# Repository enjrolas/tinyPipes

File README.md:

## TinyPipes git repo
===

Welcome to the tinyPipes git repo!  This is the home of all the hardware and firmware for tinyPipes electronics.  This should give you a basic idea of where everything lives, and how to use the repo.  Ready?  Onwards!

The repo has a pretty simple structure:

	/
	|
	+Firmware/
	|	|
	|	+bootloader/
	|	|
	|	+libraries/
	|	|
	|	+utilities/
	|	|
	|	+wetware/
	|	|
	|	+Shipped Firmware/
	|
	+Hardware/
		|
		+gerbers/
		|
		+demo/
		|
		+proto/

Firmware/

This is where all firmware lives.  The tinyPipes firmware is called wetware.  It's all based around Arduino C and compilable in arduino 1.0 and later.  

Install everything in libraries/ into the libraries folder in your Arduino sketch folder.

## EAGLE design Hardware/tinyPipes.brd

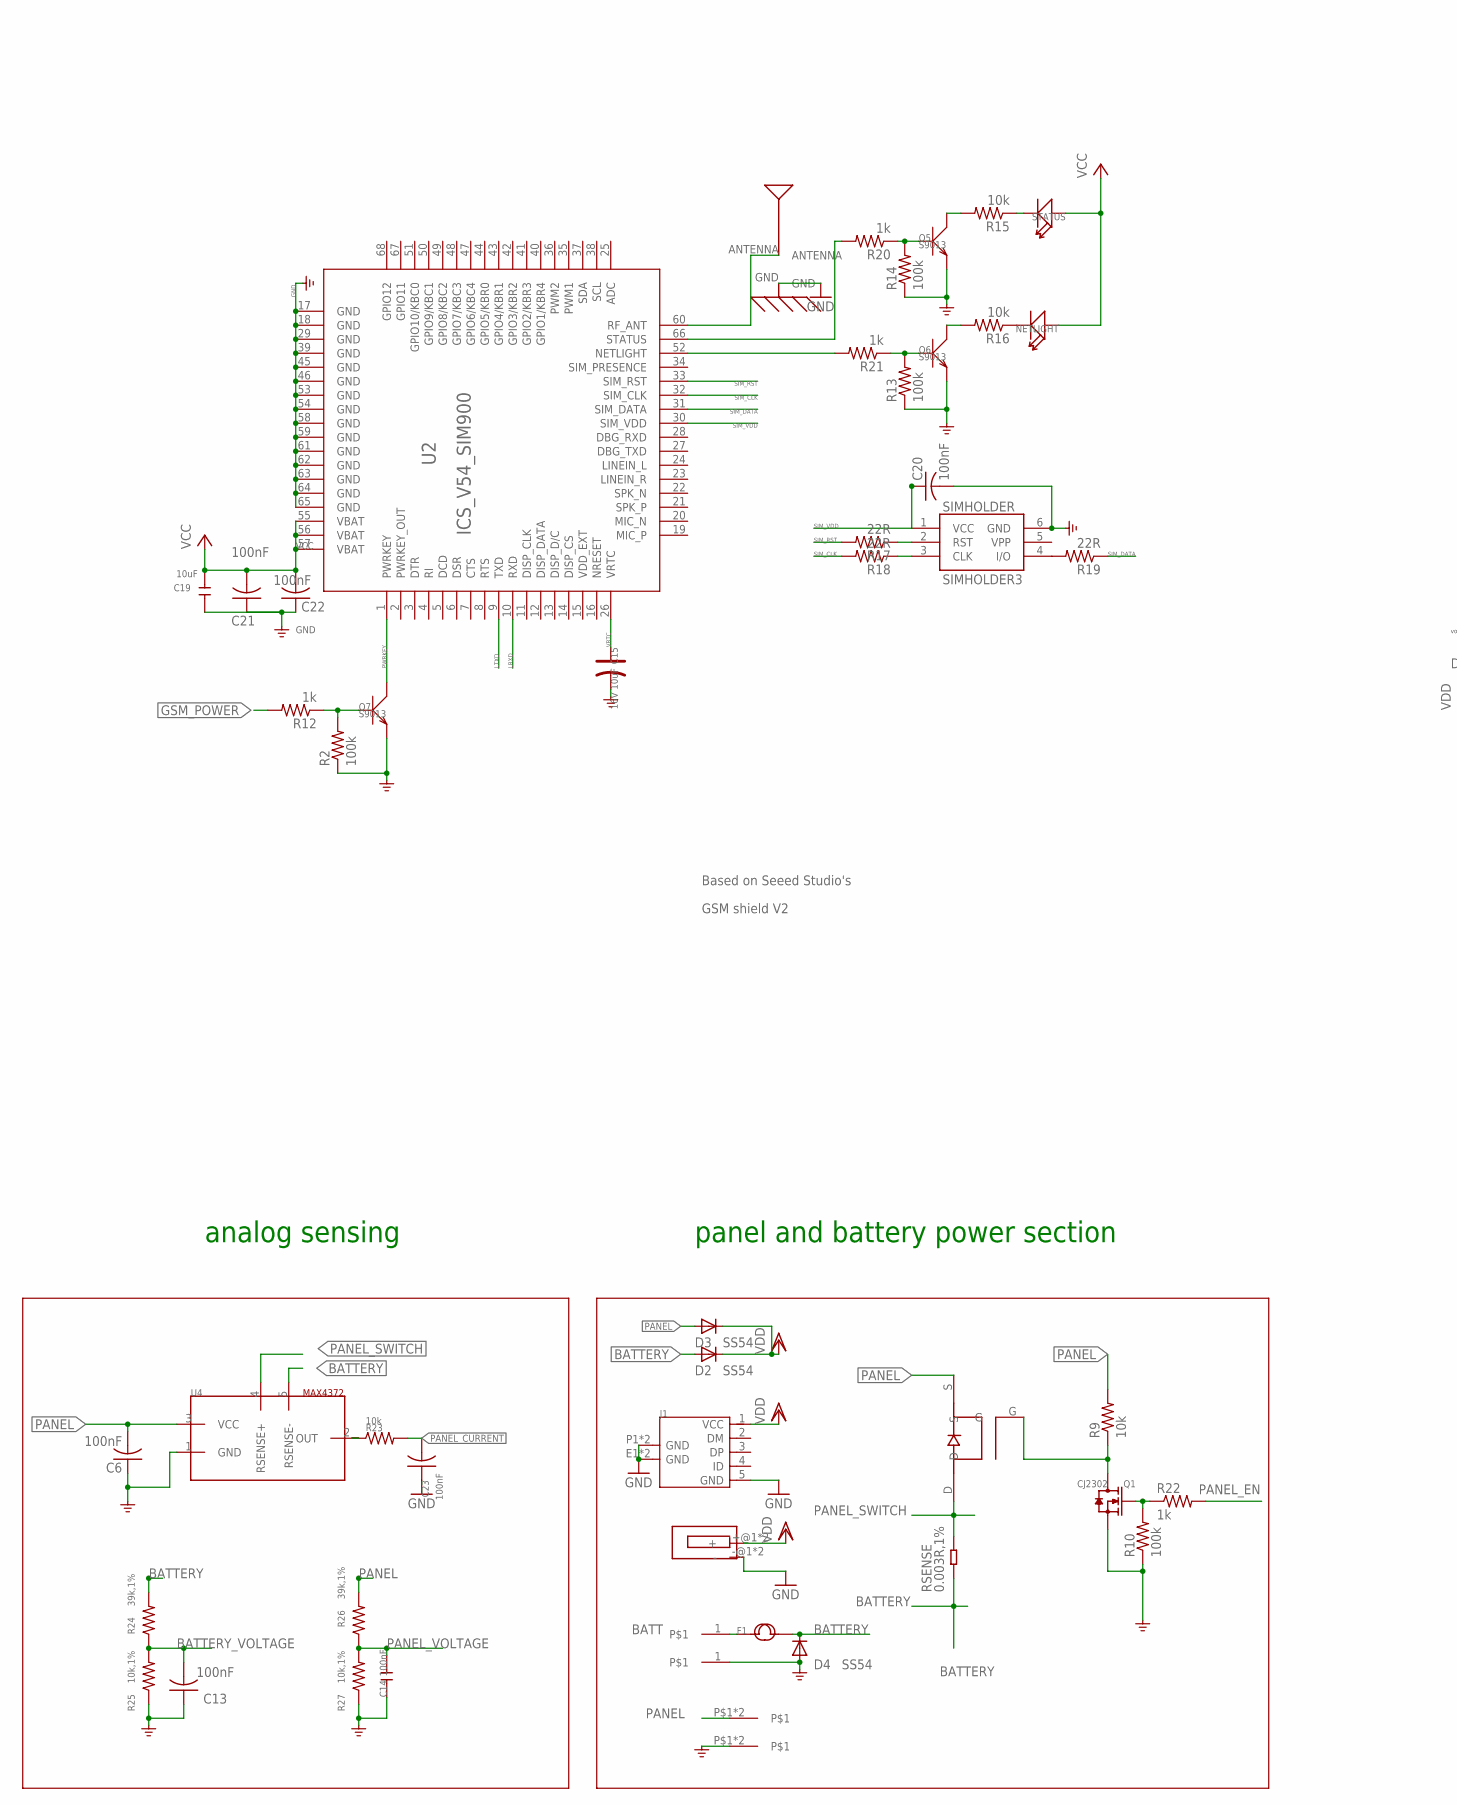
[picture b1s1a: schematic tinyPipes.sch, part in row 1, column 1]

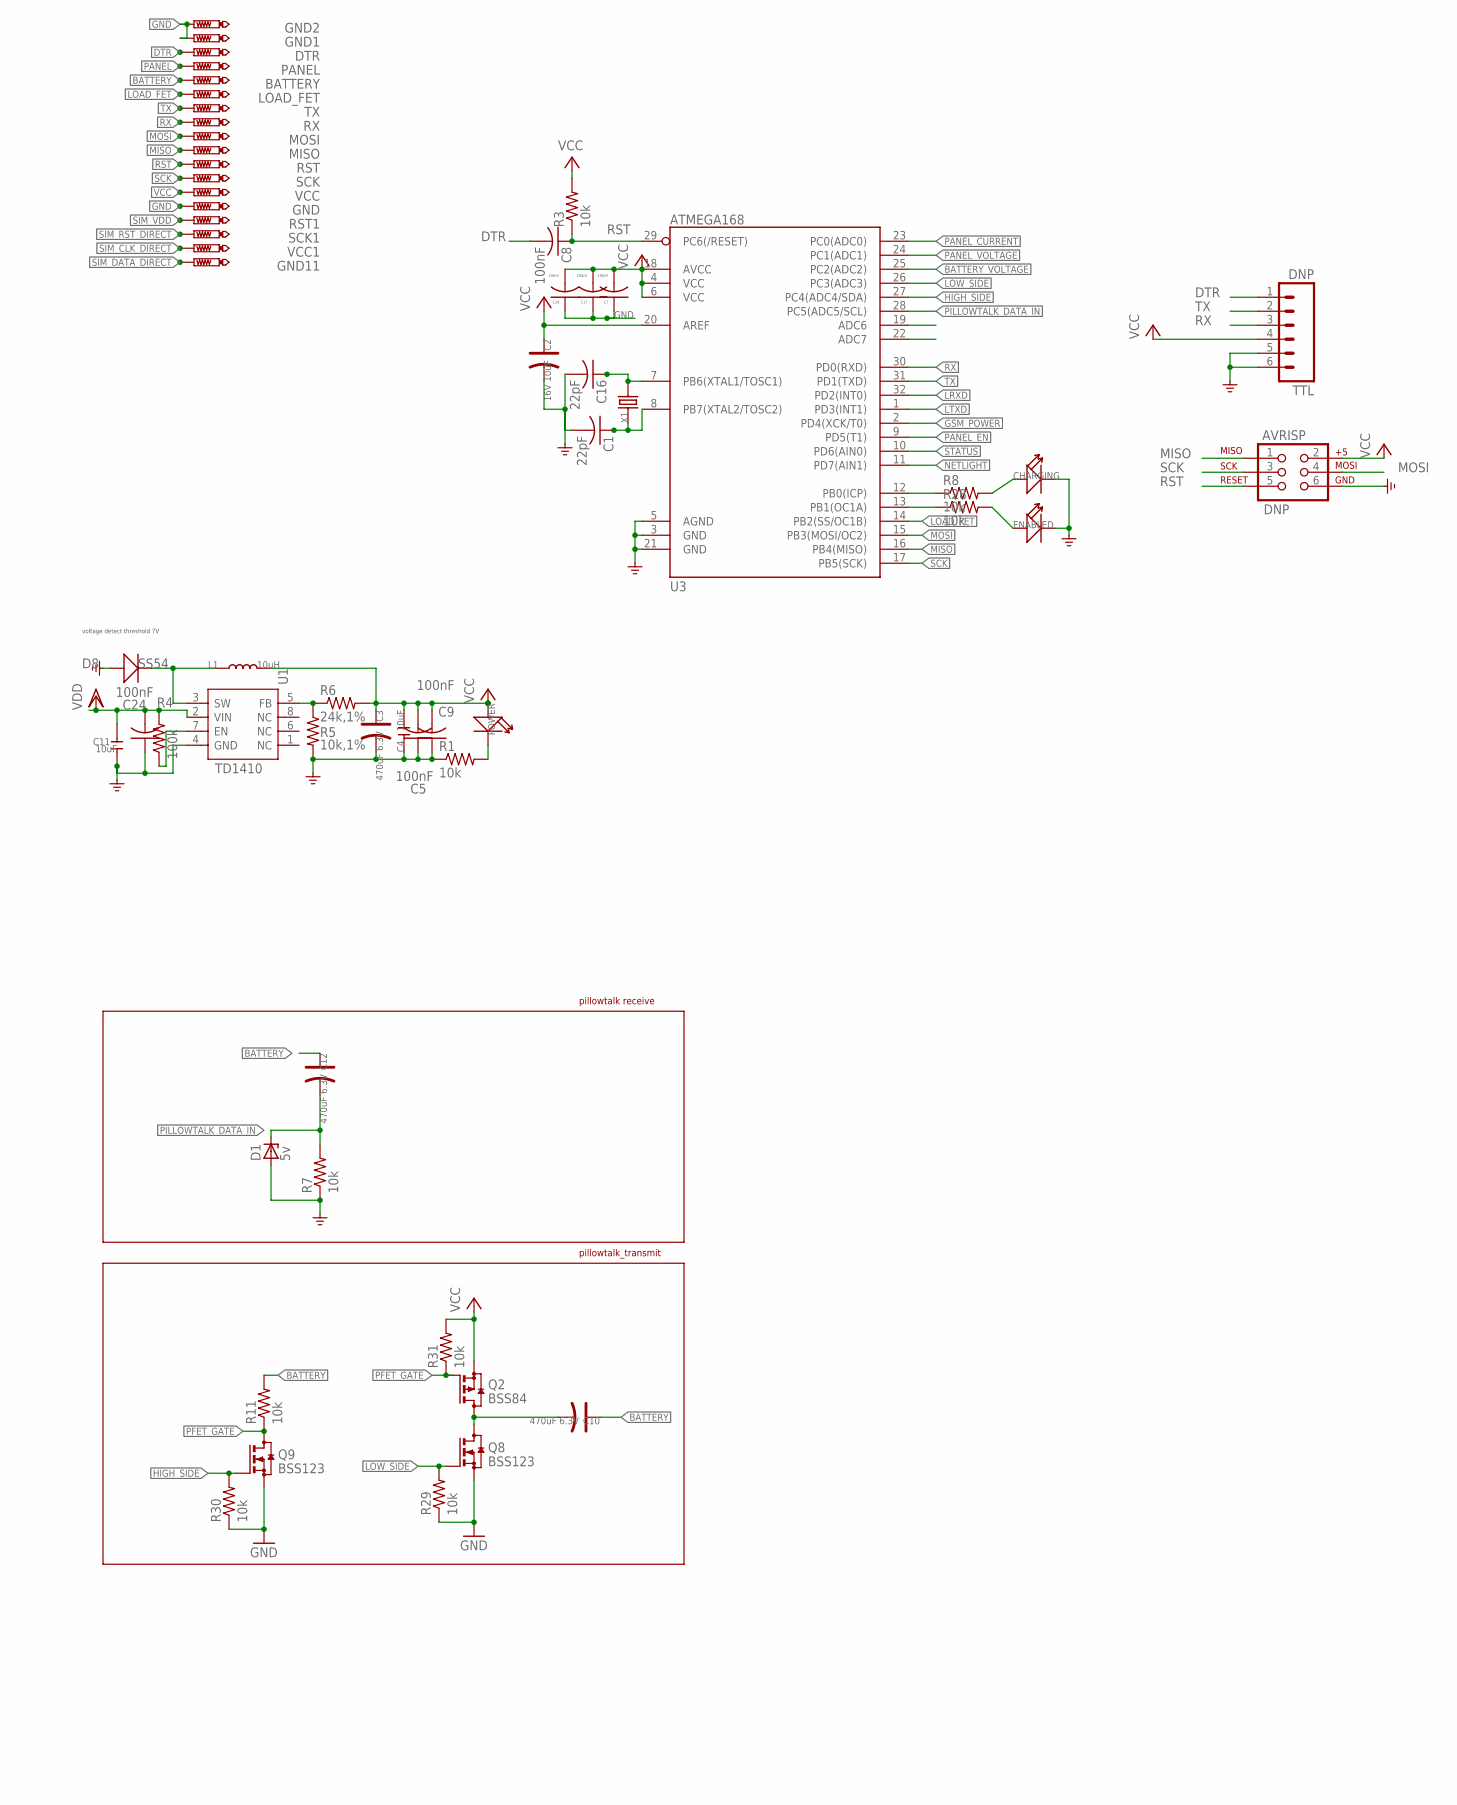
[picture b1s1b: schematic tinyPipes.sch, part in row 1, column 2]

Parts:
AVRISP: DNP; 2X3_LOCK
BATTERY: HEARTPAD; HEART
BATTERY+: TINYPIPES_BATTBATT; TINYPIPES_BATT
BATTERY-: TINYPIPES_BATTBATT; TINYPIPES_BATT
C1, C16: 22pF; C0402
C2, C15: 16V 10uF; AVX-A
C3, C10, C12: 470uF 6.3V; AVX-D
C4, C11, C19: 10uF; C0805
C5, C6, C7, C8, C9, C13, C17, C18, C20, C21, C22, C23, C24: 100nF; C0402
C14: 100nF; C0603
CHARGING: LED'0603'; LED-0603
D1: 5v; SOT23
D2, D3, D4, D8: SS54; SMB
DTR: HEARTPAD; HEART
ENABLED: LED'0603'; LED-0603
F1: FUSE'16R700'; 0210
GND, GND1, GND2, GND11: HEARTPAD; HEART
J1: Micro-USB connector; B-SMD-5P
L1: 10uH; L0630
LOAD_FET: HEARTPAD; HEART
MISO: HEARTPAD; HEART
MOSI: HEARTPAD; HEART
NETLIGHT: LED'0603'; LED-0603
PANEL: HEARTPAD; HEART
PANEL+: TINYPIPES_BATTPANEL; TINYPIPES_PANEL
PANEL-: TINYPIPES_BATTPANEL; TINYPIPES_PANEL
POWER: LED'0603'; LED-0603
Q1: CJ2302; SOT23
Q2: BSS84; SOT23
Q5, Q6, Q7: S9013; SOT23
Q8, Q9: BSS123; SOT23
R1, R3, R7, R8, R9, R11, R15, R16, R23, R28, R29, R30, R31: 10k; R0402
R2, R4, R10, R13, R14: 100k; R0402
R5, R25, R27: 10k,1%; R0402
R6: 24k,1%; R0402
R12, R20, R21, R22: 1k; R0402
R17, R18, R19: 22R; R0402
R24, R26: 39k,1%; R0402
RSENSE: 0.003R,1%; R2512
RST, RST1: HEARTPAD; HEART
RX: HEARTPAD; HEART
SCK, SCK1: HEARTPAD; HEART
SIMHOLDER: SIMHOLDER3
STATUS: LED'0603'; LED-0603
TTL: DNP; 1X06_LOCK
TX: HEARTPAD; HEART
U1: TD1410; SOP8
U2: ICS_V54_SIM900
U3: ATMEGA168; TQFP32-08
U4: MAX4372; SOT23-5
U5: SI4435POWER; SO8_FET
U$1: PCB_ANTENNA; GSM_PCB_ANTENNA
U$4: BARREL_JACK; BARREL_PLUG
VCC, VCC1: HEARTPAD; HEART
X1: CRYSTAL'5032'; 2P-SMD-5X3.2

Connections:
ALT5: U3.22 (ADC7)
BATT: BATTERY+.1, F1.1
BATTERY: BATTERY.P$1, C10.+, C12.+, D2.A, D4.C, F1.2, R11.2, R24.2, RSENSE.1, U4.5 (RSENSE-)
BATTERY_VOLTAGE: C13.2, R24.1, R25.2, U3.25 (PC2(ADC2))
DTR: C8.2, DTR.P$1, TTL.1
GND: AVRISP.6, BATTERY-.1, C1.2, C2.-, C3.-, C4.1, C5.1, C6.1, C7.1, C9.1, C11.1, C13.1, C14.1, C15.-, C16.2, C17.1, C18.1, C19.1, C20.2, C21.1, C22.1, C23.1, C24.1, CHARGING.-, D1.1 (A), D4.A, D8.+, ENABLED.-, GND.P$1, GND1.P$1, GND2.P$1, J1.5 (GND), J1.E1 (GND), J1.E2 (GND), J1.P1 (GND), J1.P2 (GND), PANEL-.P$1, PANEL-.P$2, Q1.2 (S), Q5.2 (E), Q6.2 (E), Q7.2 (E), Q8.2 (S), Q9.2 (S), R1.1, R2.1, R5.2, R7.1, R10.1, R13.1, R14.1, R25.1, R27.1, R29.1, R30.1, SIMHOLDER.6 (GND), TTL.5, TTL.6, U1.4 (GND), U2.17 (GND), U2.18 (GND), U2.29 (GND), U2.39 (GND), U2.45 (GND), U2.46 (GND), U2.53 (GND), U2.54 (GND), U2.58 (GND), U2.59 (GND), U2.61 (GND), U2.62 (GND), U2.63 (GND), U2.64 (GND), U2.65 (GND), U3.3 (GND), U3.5 (AGND), U3.21 (GND), U4.1 (GND), U$1.GND, U$4.-@1 (-), U$4.-@2 (-)
GSM_POWER: R12.2, U3.2 (PD4(XCK/T0))
HIGH_SIDE: Q9.1 (G), R30.2, U3.27 (PC4(ADC4/SDA))
LOAD_FET: LOAD_FET.P$1, U3.14 (PB2(SS/OC1B))
LOW_SIDE: Q8.1 (G), R29.2, U3.26 (PC3(ADC3))
LRXD: U2.10 (RXD), U3.32 (PD2(INT0))
LTXD: U2.9 (TXD), U3.1 (PD3(INT1))
MISO: AVRISP.1, MISO.P$1, U3.16 (PB4(MISO))
MOSI: AVRISP.4, MOSI.P$1, U3.15 (PB3(MOSI/OC2))
unnamed: U2.60 (RF_ANT), U$1.ANTENNA
unnamed: C16.1, U3.7 (PB6(XTAL1/TOSC1)), X1.2
unnamed: Q6.3 (C), R16.2
unnamed: Q7.1 (B), R2.2, R12.1
unnamed: Q5.1 (B), R14.2, R20.1
unnamed: Q6.1 (B), R13.2, R21.1
unnamed: NETLIGHT.-, R16.1
unnamed: Q5.3 (C), R15.2
unnamed: POWER.-, R1.2
unnamed: R8.1, U3.12 (PB0(ICP))
unnamed: Q1.1 (G), R10.2, R22.1
unnamed: R4.1, U1.7 (EN)
unnamed: C1.1, U3.8 (PB7(XTAL2/TOSC2)), X1.1
unnamed: R28.1, U3.13 (PB1(OC1A))
unnamed: Q1.3 (D), R9.1, U5.G
unnamed: R15.1, STATUS.-
unnamed: R23.1, U4.2 (OUT)
unnamed: CHARGING.+, R8.2
unnamed: C10.-, Q2.3 (D), Q8.3 (D)
unnamed: ENABLED.+, R28.2
unnamed: D8.-, L1.1, U1.3 (SW)
unnamed: R5.1, R6.1, U1.5 (FB)
NETLIGHT: R21.2, U2.52 (NETLIGHT), U3.11 (PD7(AIN1))
PANEL: C6.2, D3.A, PANEL.P$1, PANEL+.P$1, PANEL+.P$2, R9.2, R26.2, U4.3 (VCC), U5.S
PANEL_CURRENT: C23.2, R23.2, U3.23 (PC0(ADC0))
PANEL_EN: R22.2, U3.9 (PD5(T1))
PANEL_SWITCH: RSENSE.2, U4.4 (RSENSE+), U5.D
PANEL_VOLTAGE: C14.2, R26.1, R27.2, U3.24 (PC1(ADC1))
PFET_GATE: Q2.1 (G), Q9.3 (D), R11.1, R31.1
PILLOWTALK_DATA_IN: C12.-, D1.3 (C), R7.2, U3.28 (PC5(ADC5/SCL))
PWRKEY: Q7.3 (C), U2.1 (PWRKEY)
RST: AVRISP.5, C8.1, R3.1, RST.P$1, U3.29 (PC6(/RESET))
RX: RX.P$1, TTL.3, U3.30 (PD0(RXD))
SCK: AVRISP.3, SCK.P$1, U3.17 (PB5(SCK))
SIM_CLK: R18.2, U2.32 (SIM_CLK)
SIM_CLK_DIRECT: R18.1, SIMHOLDER.3 (CLK), VCC1.P$1
SIM_DATA: R19.1, U2.31 (SIM_DATA)
SIM_DATA_DIRECT: GND11.P$1, R19.2, SIMHOLDER.4 (I/O)
SIM_RST: R17.2, U2.33 (SIM_RST)
SIM_RST_DIRECT: R17.1, SCK1.P$1, SIMHOLDER.2 (RST)
SIM_VDD: C20.1, RST1.P$1, SIMHOLDER.1 (VCC), U2.30 (SIM_VDD)
STATUS: R20.2, U2.66 (STATUS), U3.10 (PD6(AIN0))
TX: TTL.2, TX.P$1, U3.31 (PD1(TXD))
VCC: AVRISP.2, C2.+, C3.+, C4.2, C5.2, C7.2, C9.2, C17.2, C18.2, C19.2, C21.2, C22.2, L1.2, NETLIGHT.+, POWER.+, Q2.2 (S), R3.2, R6.2, R31.2, STATUS.+, TTL.4, U2.55 (VBAT), U2.56 (VBAT), U2.57 (VBAT), U3.4 (VCC), U3.6 (VCC), U3.18 (AVCC), U3.20 (AREF), VCC.P$1
VDD: C11.2, C24.2, D2.C, D3.C, J1.1 (VCC), R4.2, U1.2 (VIN), U$4.+@1 (+), U$4.+@2 (+)
VRTC: C15.+, U2.26 (VRTC)
`: U3.19 (ADC6)

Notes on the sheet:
Based on Seeed Studio's
GSM shield V2
voltage detect threshold 7V
panel and battery power section
analog sensing
pillowtalk receive
pillowtalk_transmit

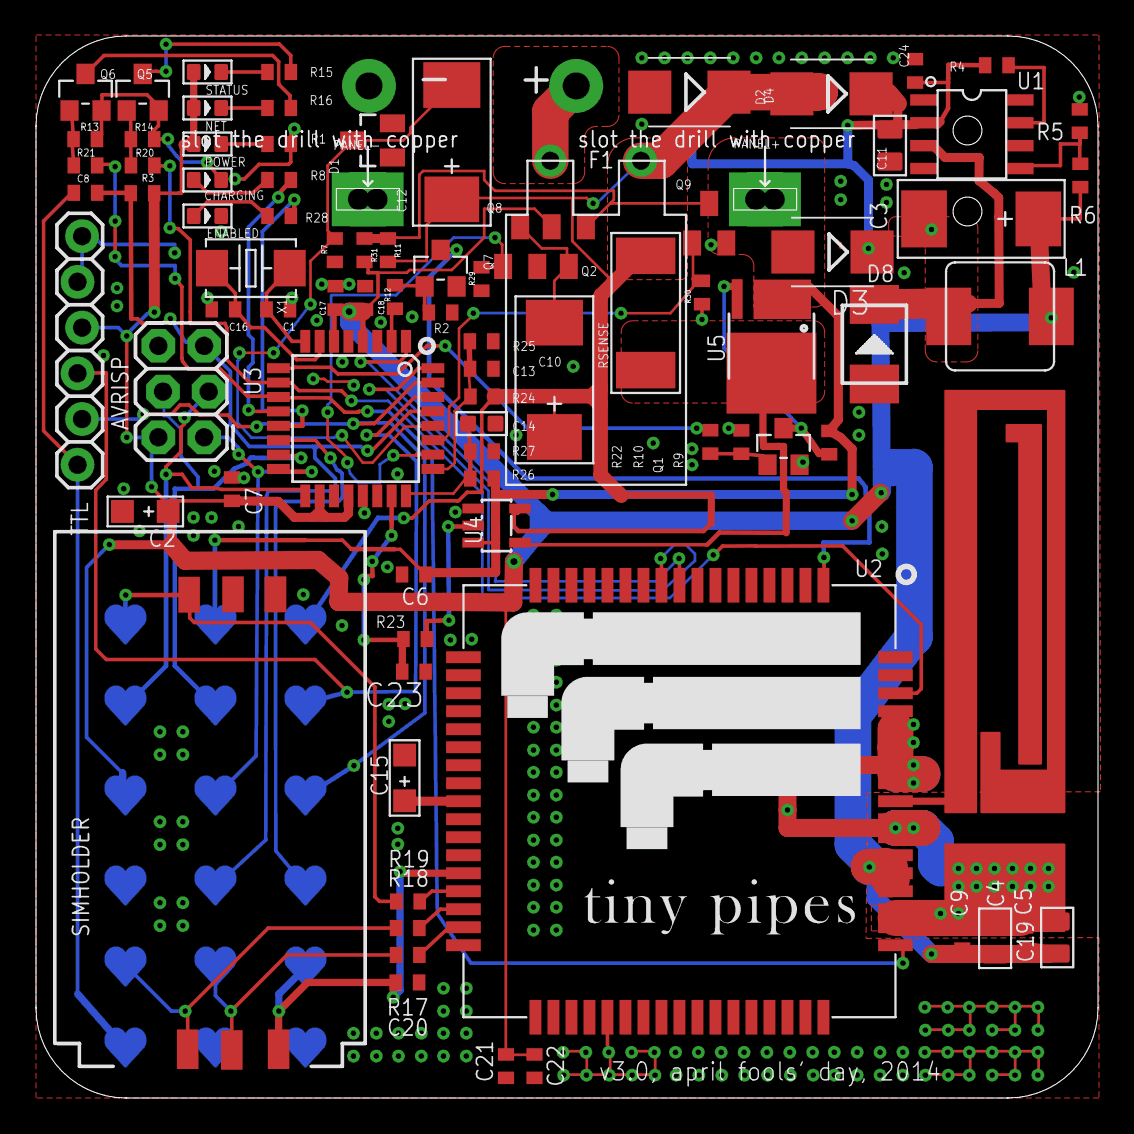
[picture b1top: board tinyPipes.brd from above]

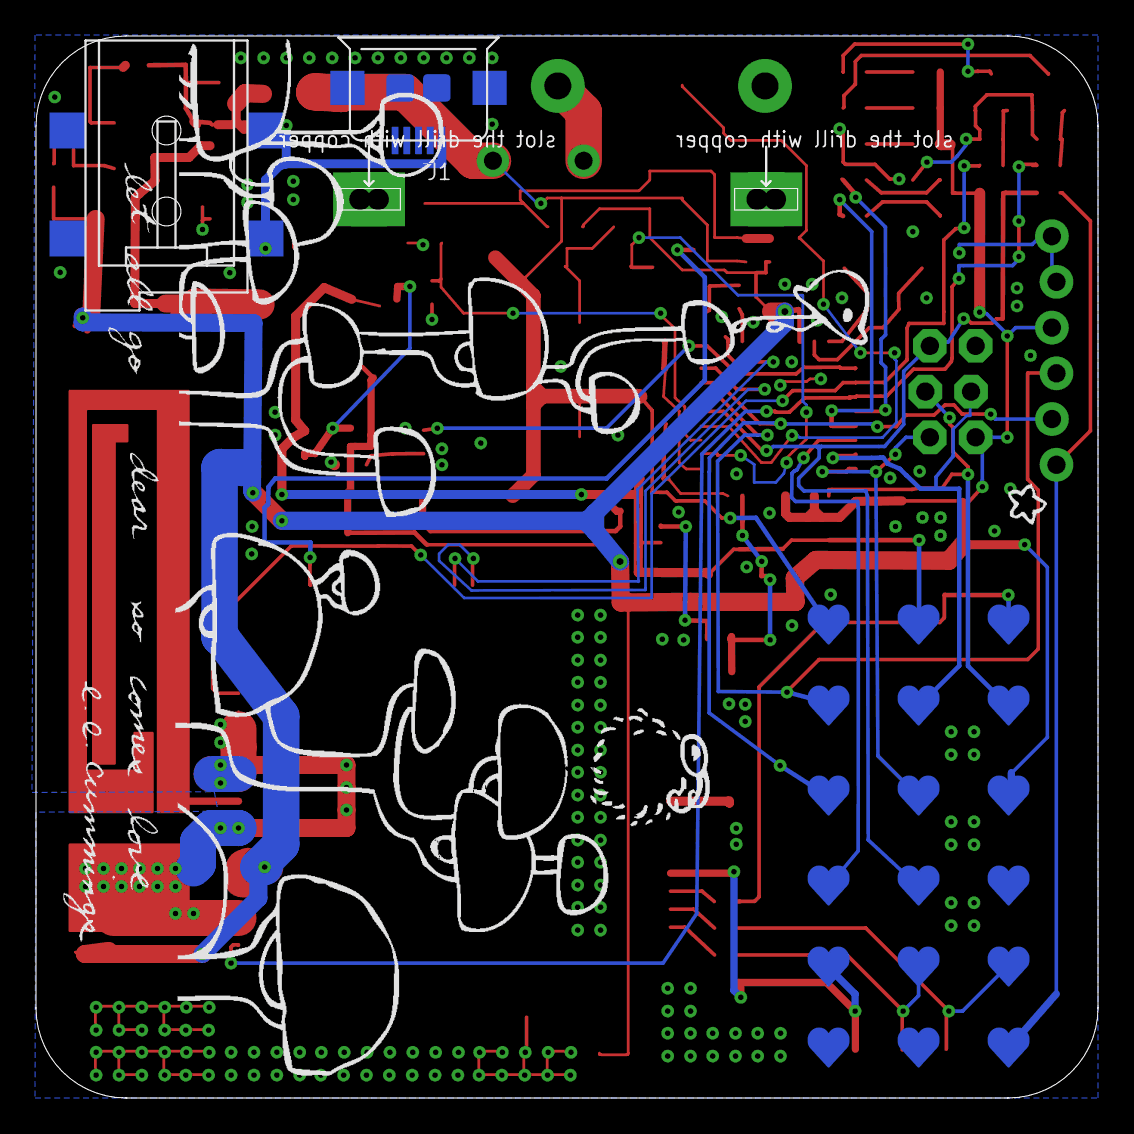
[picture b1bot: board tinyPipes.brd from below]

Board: 2 copper layers, 59.0 x 59.0 mm, 109 parts (20 on the bottom side), 59 nets.

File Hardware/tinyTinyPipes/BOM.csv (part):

Partlist

Exported from tinyPipes-tinyComponents.brd at 1/12/14 2:02 AM

EAGLE Version 6.5.0 Copyright (c) 1988-2013 CadSoft

Assembly variant: 

Part      Value               Package         Library             Position (mm)         Orientation

ANT1                          4P-U-FL         Connector           (55.29 16.74)         R0
B+        TINYPIPES_BATTBATT  TINYPIPES_BATT  tinyPipes v2.6      (30.734 56.388)       R0
B-        TINYPIPES_BATTBATT  TINYPIPES_BATT  tinyPipes v2.6      (22.225 49.53)        R0
BATTERY   PTR1B2,54           B2,54           testpad             (19 26.5)             MR0
BM        TINYPIPES_BATTSBATT TINYPIPES_SBATT tinyPipes v2.6      (24.003 42.291)       R0
BP        TINYPIPES_BATTSBATT TINYPIPES_SBATT tinyPipes v2.6      (27.972 42.489)       R0
C1        22pF                C0201           rcl                 (14.939 43.462)       R90
C2        16V 10uF            AVX-A           Discrete            (7.493 32.893)        R180
C3        470uF 6.3V          AVX-D           Discrete            (53.3895 36.953)      R180
C4        10uF                C0402           rcl                 (57.032 32.737)       R90
C5        100nF               C0402           rcl                 (55.157 32.864)       R90
C6        100nF               C0402           rcl                 (25.173 45.169)       R90
C7        100nF               C0402           rcl                 (6.866 34.346)        R0
C8        100nF               C0402           rcl                 (10.16 37.084)        R180
C9        100nF               C0402           rcl                 (53.603 32.864)       R90
C10       100nF               C0402           rcl                 (44.815 36.393)       R90
C11       10uF                C0402           rcl                 (55.513 48.5555)      R180
C12       100nF               C0402           rcl                 (36.624 36.393)       R90
C13       100nF               C0402           rcl                 (34.557 35.297)       R0
C14       100nF               C0402           rcl                 (34.577 34.145)       R0
C15       16V 10uF            AVX-A           Discrete            (25.511 18.034)       R90
C16       22pF                C0201           rcl                 (15.561 43.476)       R90
C17       100nF               C0402           rcl                 (11.637 33.45)        R270
C18       100nF               C0402           rcl                 (23.288 33.45)        R270
C19       10uF                C0805           Discrete            (53.848 11.176)       R90
C20       100nF               C0603           Discrete            (25.8275 13.1665)     R90
C21       100nF               C0402           rcl                 (57.15 11.303)        R90
C22       100nF               C0402           rcl                 (55.626 11.303)       R90
C23       100nF               C0402           rcl                 (31.204 45.291)       R270
C24       100nF               C0402           rcl                 (46.3665 48.682)      R90
C25       100nF               C0402           rcl                 (26.515 45.16)        R90
C26       0.1uF               C0402           rcl                 (27 34)               R180
D2        SS54                SMB             diode               (45.742 55.886)       R180
D4        SS54                SMB             diode               (36.3 55.88)          R180
D8        SS54                SMB             Discrete            (46.577 41.876)       R90
DTR       PTR1B2,54           B2,54           testpad             (9 3)                 MR0
F1                            0210            tinyPipes v2.6      (31.369 52.07)        R0
F2                            0210            tinyPipes v2.6      (2.731 53.213)        R90
GND       PTR1B2,54           B2,54           testpad             (9 12)                MR0
GND2      PTR1B2,54           B2,54           testpad             (14 3)                MR0
GND3      PTR1B2,54           B2,54           testpad             (19 3)                MR0
GND11     PTR1B2,54           B2,54           testpad             (9 26.5)              MR0
L1        10uH                L0630           Discrete            (53.727 42.6655)      R0
LOAD_FET  PTR1B2,54           B2,54           testpad             (19 12)               MR0
MISO      PTR1B2,54           B2,54           testpad             (14 17)               MR0
MOSI      PTR1B2,54           B2,54           testpad             (14 22)               MR0
NETLIGHT                      LED-0603        Discrete            (2.589 39.482)        R270
OUT+      TINYPIPES_BATTBATT  TINYPIPES_BATT  tinyPipes v2.6      (2.683 46.8)          R0
OUT-      TINYPIPES_BATTBATT  TINYPIPES_BATT  tinyPipes v2.6      (22.225 52.578)       R0
PANEL     PTR1B2,54           B2,54           testpad             (14 26.5)             MR0
PANEL+    TINYPIPES_BATTPANEL TINYPIPES_PANEL tinyPipes_v2.5      (40.504 49.928)       R180
PANEL-    TINYPIPES_BATTPANEL TINYPIPES_PANEL tinyPipes_v2.5      (18.438 49.928)       R180
POWER                         LED-0603        Discrete            (0.97 39.482)         R270
Q1        CJ2302              SOT23           Discrete            (41.529 36.449)       R0
Q2        IRF5305             TO263           transistor-power    (9.382 50.097)        R180
Q3        CJ2302              SOT23           Discrete            (15.216 53.978)       R0
Q5        S9013               SOT23           Discrete            (7.329 37.116)        R270
Q6        S9013               SOT23           Discrete            (2.809 33.678)        R270
Q7        S9013               SOT23           Discrete            (47.852 32.601)       R0
R1        10k                 R0201           rcl                 (1.03 37.388)         R90
R2        100k                R0201           rcl                 (48.712 30.438)       R270
R3        10k                 R0201           rcl                 (10.671 36.08)        R180
R4        100k                R0201           rcl                 (55.226 49.765)       R0
R5        10k, 1%             R0201           rcl                 (55.08 47.483)        R0
R6        24k, 1%             R0201           rcl                 (55.06 46.93)         R0
R7        10k                 R0201           rcl                 (45.913 36.738)       R270
R8        10k                 R0201           rcl                 (30.575 48.408)       R270
R9        10k                 R0201           rcl                 (43.572 36.4095)      R90
R10       100k                R0201           rcl                 (39.185 36.4415)      R270
R11       10k                 R0201           rcl                 (37.736 36.478)       R270
R12       1k                  R0201           rcl                 (46.939 30.45)        R270
R13       100k                R0201           rcl                 (0.758 33.5855)       R90
R14       100k                R0201           rcl                 (5.229 36.972)        R90
R15       10k                 R0201           rcl                 (4.208 37.418)        R270
R16       10k                 R0201           rcl                 (2.589 37.338)        R270
R17       22R                 R0201           rcl                 (24.683 8.199)        R0
R18       22R                 R0201           rcl                 (24.683 8.962)        R0
R19       22R                 R0201           rcl                 (24.669 9.618)        R180
R20       1k                  R0201           rcl                 (11.94 39.752)        R0
R21       1k                  R0201           rcl                 (11.97 38.938)        R0
R22       1k                  R0201           rcl                 (38.465 36.449)       R90
R23       10k                 R0201           rcl                 (31.249 48.388)       R270
R24       39k, 1%             R0201           rcl                 (24.757 47.556)       R90
R25       10k, 1%             R0201           rcl                 (25.5995 47.5575)     R90
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
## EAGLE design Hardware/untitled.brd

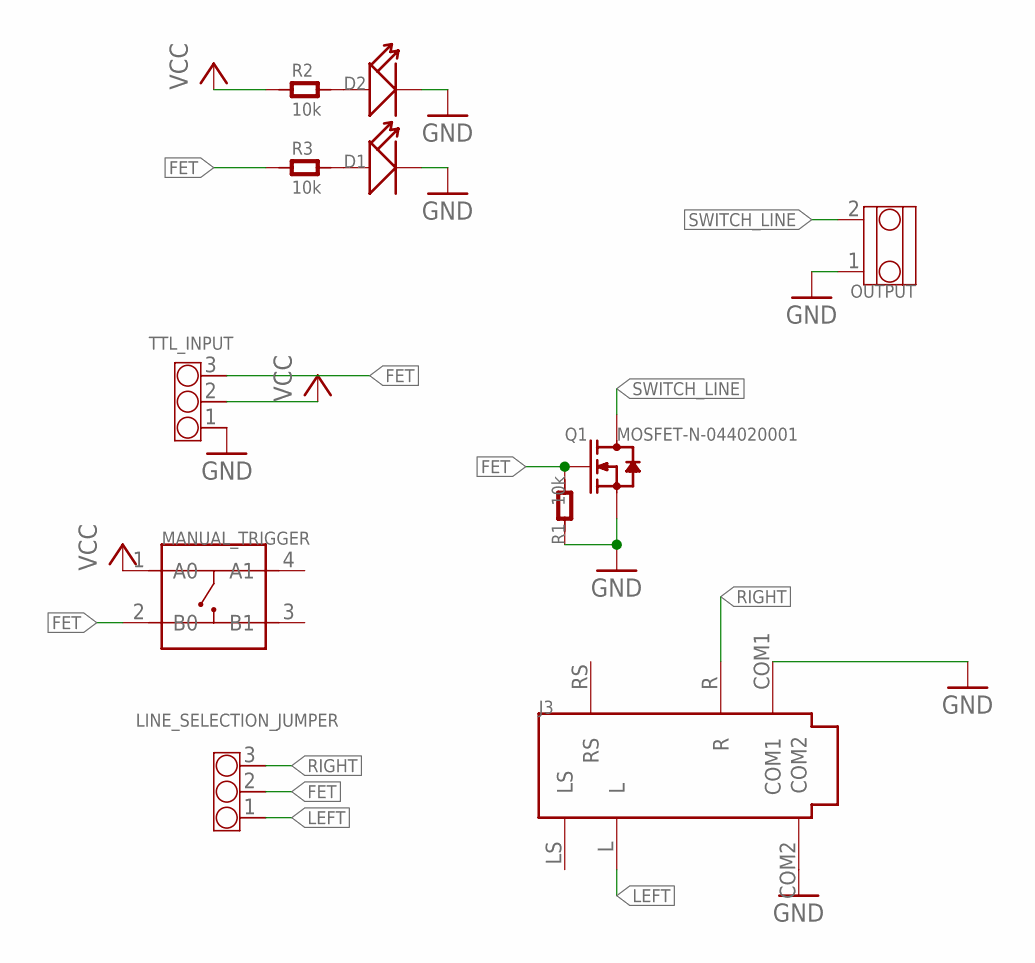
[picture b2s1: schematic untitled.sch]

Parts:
D1, D2: LED; LED0603
J3: AUDIO-CONNECTOR-6P-SMD-3440030P1; 6P-SMD-3.5
LINE_SELECTION_JUMPER: CONNECTOR-HEADER-3P-3460810P1; 1X3P-2.54-2.54-11.6-3.0-BLACK-MALE
MANUAL_TRIGGER: manual data; 4P-SMD-6.0X6.0X5.0H
OUTPUT: SCREW-TERMINAL-2P-3470070P1; 2P-3.5
Q1: MOSFET-N-044020001; SOT23
R1, R2, R3: 10k; R0603
TTL_INPUT: CONNECTOR-HEADER-3P-3460810P1; 1X3P-2.54-2.54-11.6-3.0-BLACK-MALE

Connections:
FET: LINE_SELECTION_JUMPER.2, MANUAL_TRIGGER.2 (B0), Q1.1 (G), R1.2, R3.1, TTL_INPUT.3
GND: D1.-, D2.-, J3.COM1, J3.COM2, OUTPUT.1, Q1.2 (S), R1.1, TTL_INPUT.1
LEFT: J3.L, LINE_SELECTION_JUMPER.1
unnamed: D1.+, R3.2
unnamed: D2.+, R2.2
RIGHT: J3.R, LINE_SELECTION_JUMPER.3
SWITCH_LINE: OUTPUT.2, Q1.3 (D)
VCC: MANUAL_TRIGGER.1 (A0), R2.1, TTL_INPUT.2

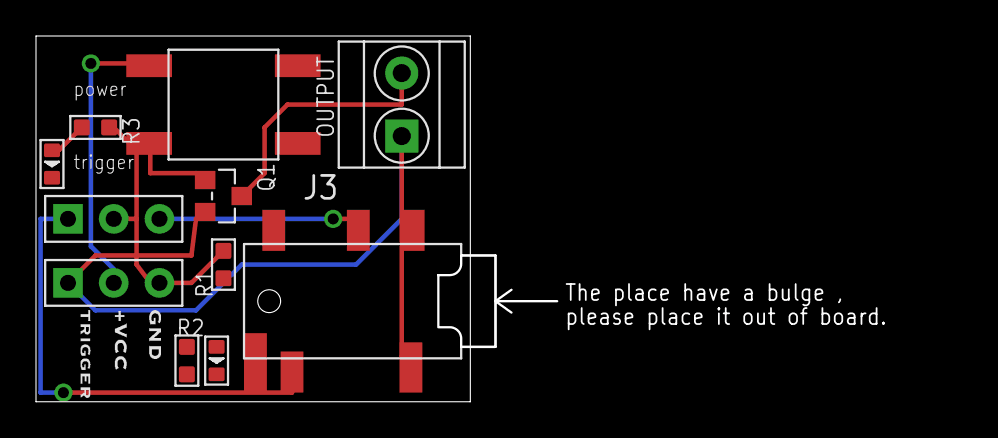
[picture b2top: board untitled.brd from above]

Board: 2 copper layers, 24.1 x 20.3 mm, 11 parts (0 on the bottom side), 8 nets.

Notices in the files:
parts and their libraries:
SparkFun: Licensing: CC v3.0 Share-Alike You are welcome to use this library for commercial purposes.
